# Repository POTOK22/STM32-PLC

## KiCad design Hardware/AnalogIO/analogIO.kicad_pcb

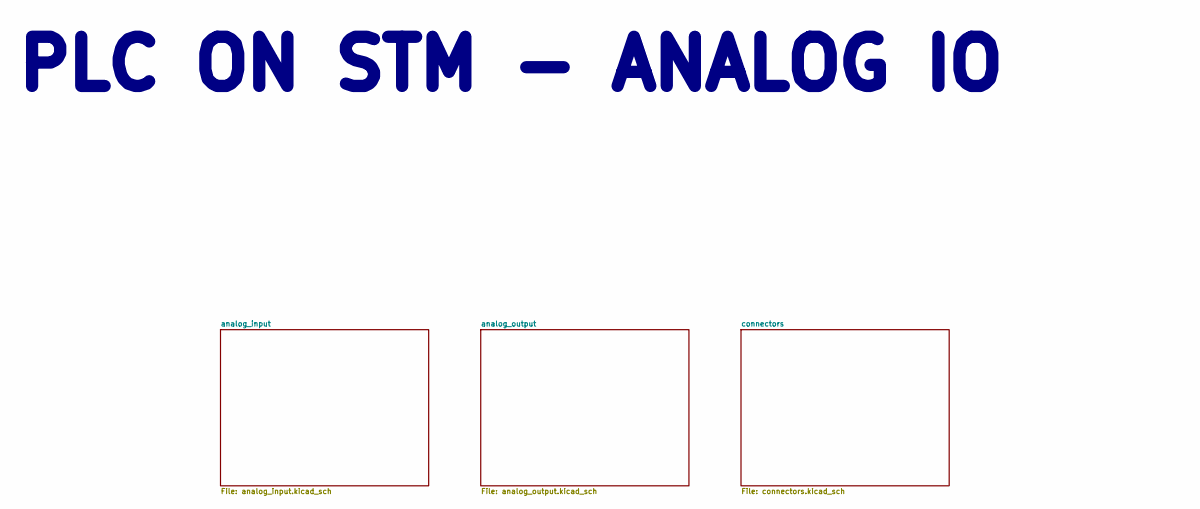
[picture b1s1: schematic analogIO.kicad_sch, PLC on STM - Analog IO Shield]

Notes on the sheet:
PLC ON STM - ANALOG IO

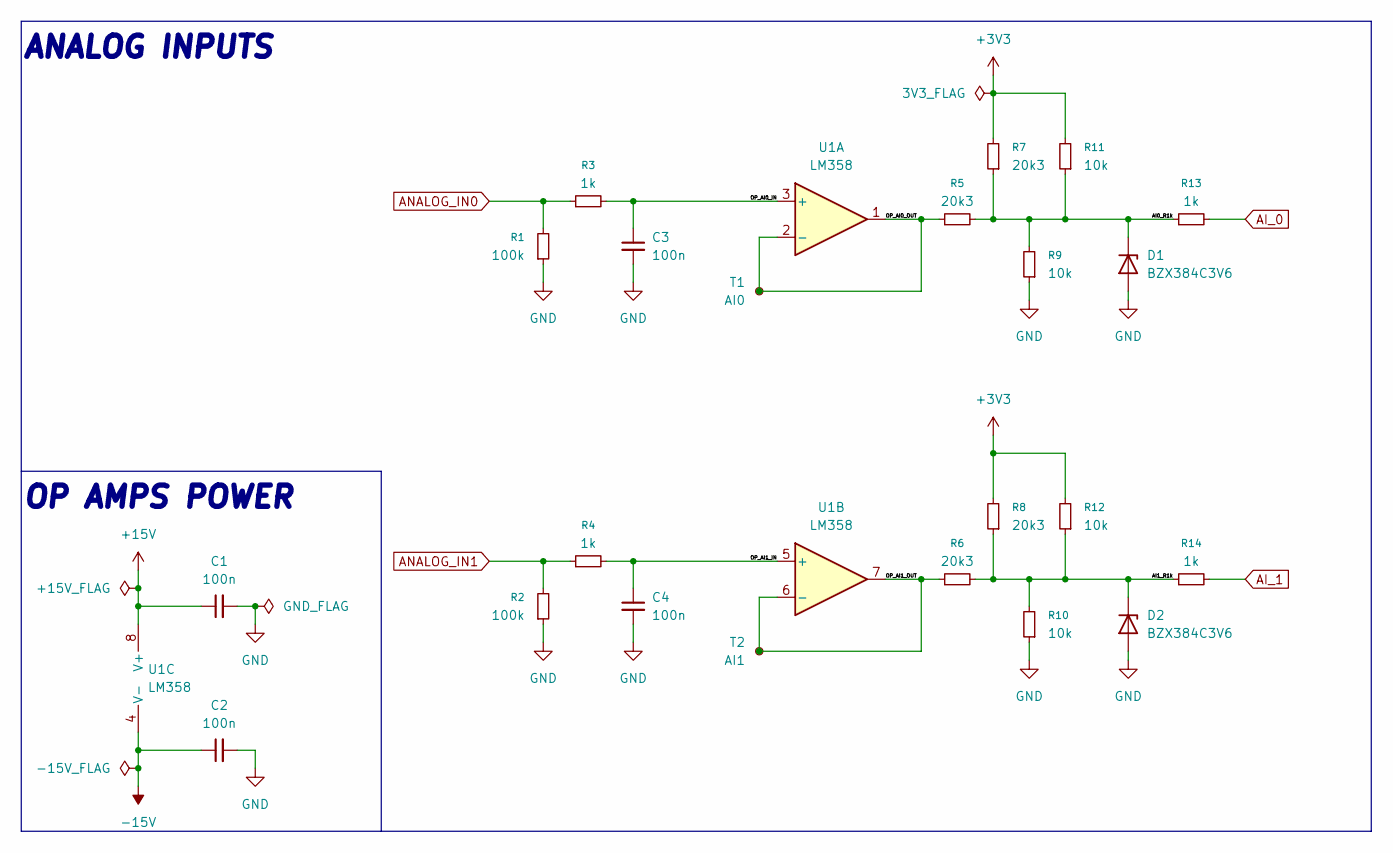
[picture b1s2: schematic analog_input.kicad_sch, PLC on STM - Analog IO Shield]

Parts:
C1, C2, C3, C4: 100n; C_0603_1608Metric_Pad1.08x0.95mm_HandSolder; Mouser Part Number GRM033R6YA104ME14D
D1, D2: BZX384C3V6; D_SOD-323; Mouser Part Number 78-BZX384C3V6-HE3-08
R1, R2: 100k; R_0603_1608Metric_Pad0.98x0.95mm_HandSolder; Mouser Part Number 603-RT0603DRE07100KL
R3, R4, R13, R14: 1k; R_0603_1608Metric_Pad0.98x0.95mm_HandSolder; Mouser Part Number 71-CRCW06031K00FKED
R5, R6, R7, R8: 20k3; R_0603_1608Metric_Pad0.98x0.95mm_HandSolder; Mouser Part Number 71-CRCW0603-20.5K-E3
R9, R10, R11, R12: 10k; R_0603_1608Metric_Pad0.98x0.95mm_HandSolder; Mouser Part Number 71-CRCW0603-10K-E3
T1: AI0; TestPoint_Pad_1.0x1.0mm
T2: AI1; TestPoint_Pad_1.0x1.0mm
U1: LM358; SOIC-8_3.9x4.9mm_P1.27mm; Mouser Part Number 511-LM358D

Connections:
+3V3: R7.2, R8.2, R11.2, R12.2; also elsewhere on the board
+15V: C1.1, U1.8 (V+); also elsewhere on the board
-15V: C2.1, U1.4 (V-); also elsewhere on the board
/analog_input/AI0_R1k: D1.1 (K), R5.2, R7.1, R9.2, R11.1, R13.1
/analog_input/AI1_R1k: D2.1 (K), R6.2, R8.1, R10.2, R12.1, R14.1
/analog_input/OP_AI0_IN: C3.1, R3.2, U1.3 (+)
/analog_input/OP_AI0_OUT: R5.1, T1.1, U1.1, U1.2 (-)
/analog_input/OP_AI1_IN: C4.1, R4.2, U1.5 (+)
/analog_input/OP_AI1_OUT: R6.1, T2.1, U1.6 (-), U1.7
AI_0: R13.2; also elsewhere on the board
AI_1: R14.2; also elsewhere on the board
ANALOG_IN0: R1.2, R3.1; also elsewhere on the board
ANALOG_IN1: R2.2, R4.1; also elsewhere on the board
GND: C1.2, C2.2, C3.2, C4.2, D1.2 (A), D2.2 (A), R1.1, R2.1, R9.1, R10.1; also elsewhere on the board

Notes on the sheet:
OP AMPS POWER
ANALOG INPUTS

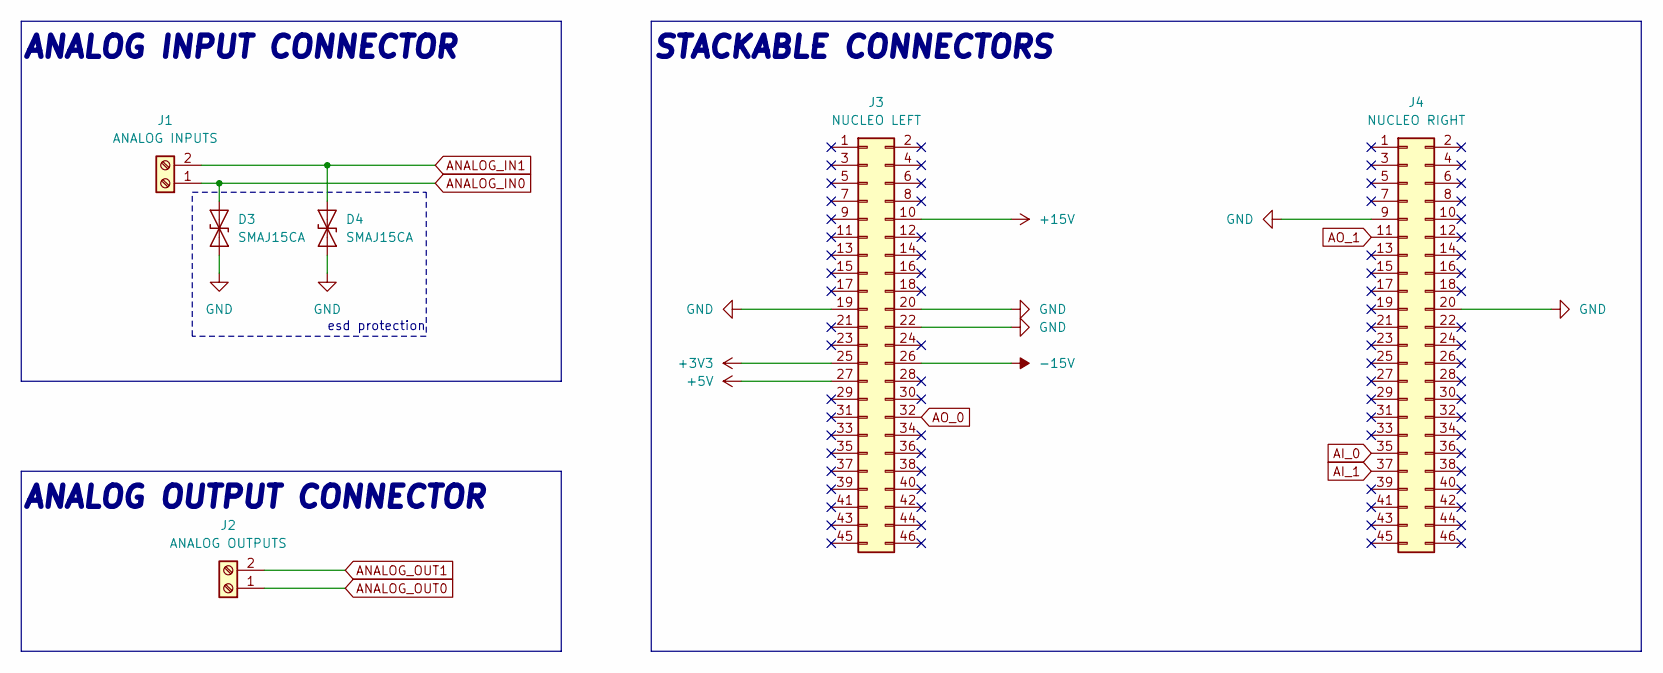
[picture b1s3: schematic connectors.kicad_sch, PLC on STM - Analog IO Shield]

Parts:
D3, D4: SMAJ15CA; D_SMA; Mouser Part Number 576-SMBJ15CA
J1: ANALOG INPUTS; 1725656; Mouser Part Number 651-1725656
J2: ANALOG OUTPUTS; 1725656; Mouser Part Number 651-1725656
J3: NUCLEO LEFT; PRT12790; Mouser Part Number 474-PRT-12790
J4: NUCLEO RIGHT; PRT12790; Mouser Part Number 474-PRT-12790

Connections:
+3V3: J3.25; also elsewhere on the board
+5V: J3.27; also elsewhere on the board
+15V: J3.10; also elsewhere on the board
-15V: J3.26; also elsewhere on the board
AI_0: J4.35; also elsewhere on the board
AI_1: J4.37; also elsewhere on the board
ANALOG_IN0: D3.2 (A2), J1.1; also elsewhere on the board
ANALOG_IN1: D4.2 (A2), J1.2; also elsewhere on the board
ANALOG_OUT0: J2.1; also elsewhere on the board
ANALOG_OUT1: J2.2; also elsewhere on the board
AO_0: J3.32; also elsewhere on the board
AO_1: J4.11; also elsewhere on the board
GND: D3.1 (A1), D4.1 (A1), J3.19, J3.20, J3.22, J4.9, J4.20; also elsewhere on the board

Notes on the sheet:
ANALOG INPUT CONNECTOR
STACKABLE CONNECTORS
esd protection
ANALOG OUTPUT CONNECTOR

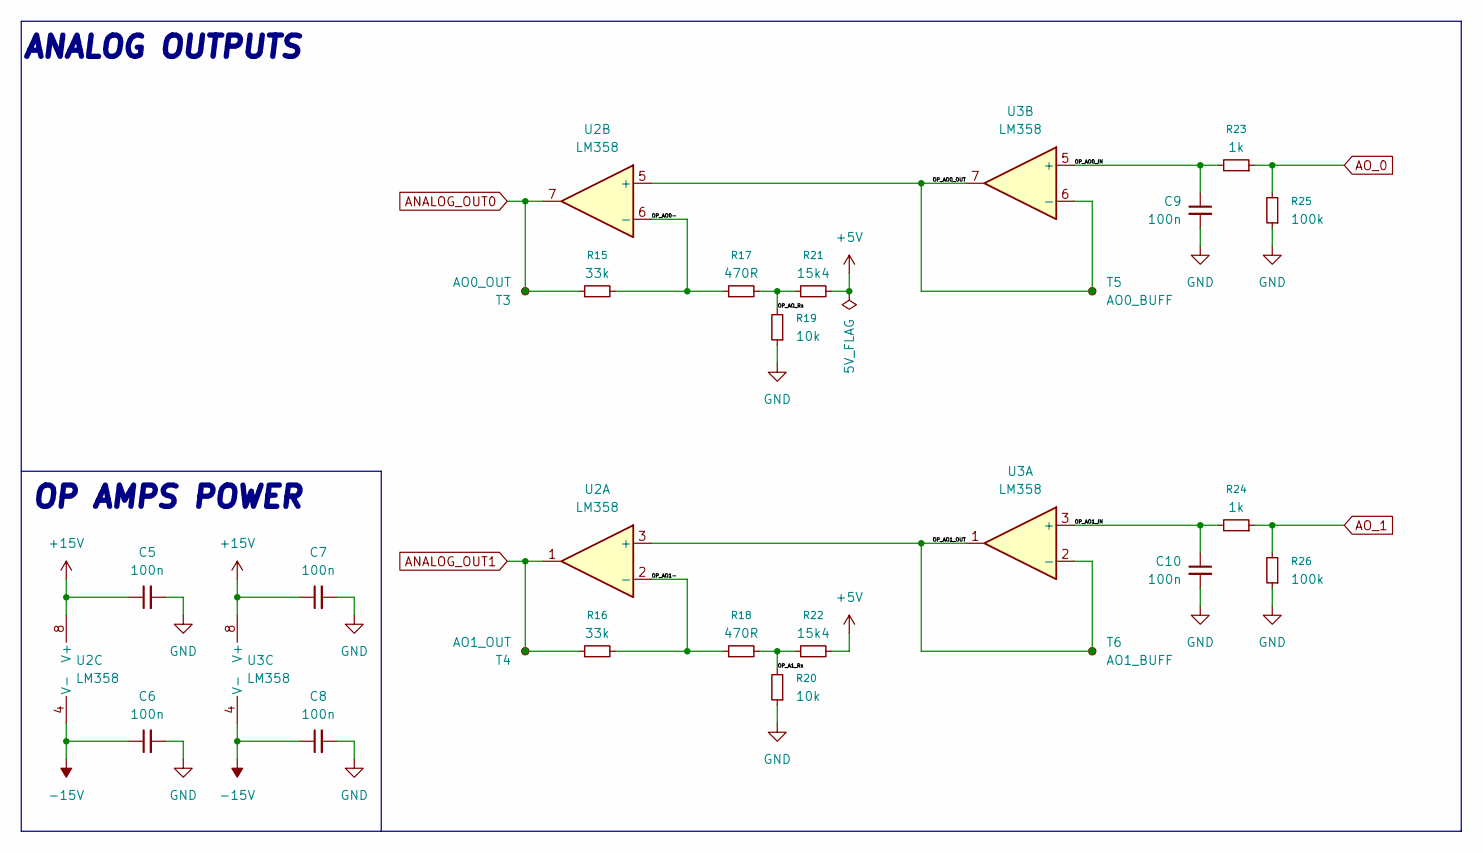
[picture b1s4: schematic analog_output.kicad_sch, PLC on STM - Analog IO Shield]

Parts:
C5, C6, C7, C8, C9, C10: 100n; C_0603_1608Metric_Pad1.08x0.95mm_HandSolder; Mouser Part Number GRM033R6YA104ME14D
R15, R16: 33k; R_0603_1608Metric_Pad0.98x0.95mm_HandSolder; Mouser Part Number 71-CRCW0603-33K-E3
R17, R18: 470R; R_0603_1608Metric_Pad0.98x0.95mm_HandSolder; Mouser Part Number 71-CRCW0603-470-E3
R19, R20: 10k; R_0603_1608Metric_Pad0.98x0.95mm_HandSolder; Mouser Part Number 71-CRCW0603-10K-E3
R21, R22: 15k4; R_0603_1608Metric_Pad0.98x0.95mm_HandSolder; Mouser Part Number 71-CRCW0603-15.4K-E3
R23, R24: 1k; R_0603_1608Metric_Pad0.98x0.95mm_HandSolder; Mouser Part Number 71-CRCW06031K00FKED
R25, R26: 100k; R_0603_1608Metric_Pad0.98x0.95mm_HandSolder; Mouser Part Number 603-RT0603DRE07100KL
T3: AO0_OUT; TestPoint_Pad_1.0x1.0mm
T4: AO1_OUT; TestPoint_Pad_1.0x1.0mm
T5: AO0_BUFF; TestPoint_Pad_1.0x1.0mm
T6: AO1_BUFF; TestPoint_Pad_1.0x1.0mm
U2, U3: LM358; SOIC-8_3.9x4.9mm_P1.27mm; Mouser Part Number 511-LM358D

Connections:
+5V: R21.2, R22.2; also elsewhere on the board
+15V: C5.1, C7.1, U2.8 (V+), U3.8 (V+); also elsewhere on the board
-15V: C6.1, C8.1, U2.4 (V-), U3.4 (V-); also elsewhere on the board
/analog_output/OP_A1_Rs: R18.2, R20.2, R22.1
/analog_output/OP_AO0-: R15.2, R17.1, U2.6 (-)
/analog_output/OP_AO0_IN: C9.1, R23.2, U3.5 (+)
/analog_output/OP_AO0_OUT: T5.1, U2.5 (+), U3.6 (-), U3.7
/analog_output/OP_AO1-: R16.2, R18.1, U2.2 (-)
/analog_output/OP_AO1_IN: C10.1, R24.2, U3.3 (+)
/analog_output/OP_AO1_OUT: T6.1, U2.3 (+), U3.1, U3.2 (-)
/analog_output/OP_AO_Rs: R17.2, R19.2, R21.1
ANALOG_OUT0: R15.1, T3.1, U2.7; also elsewhere on the board
ANALOG_OUT1: R16.1, T4.1, U2.1; also elsewhere on the board
AO_0: R23.1, R25.2; also elsewhere on the board
AO_1: R24.1, R26.2; also elsewhere on the board
GND: C5.2, C6.2, C7.2, C8.2, C9.2, C10.2, R19.1, R20.1, R25.1, R26.1; also elsewhere on the board

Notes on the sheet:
ANALOG OUTPUTS
OP AMPS POWER

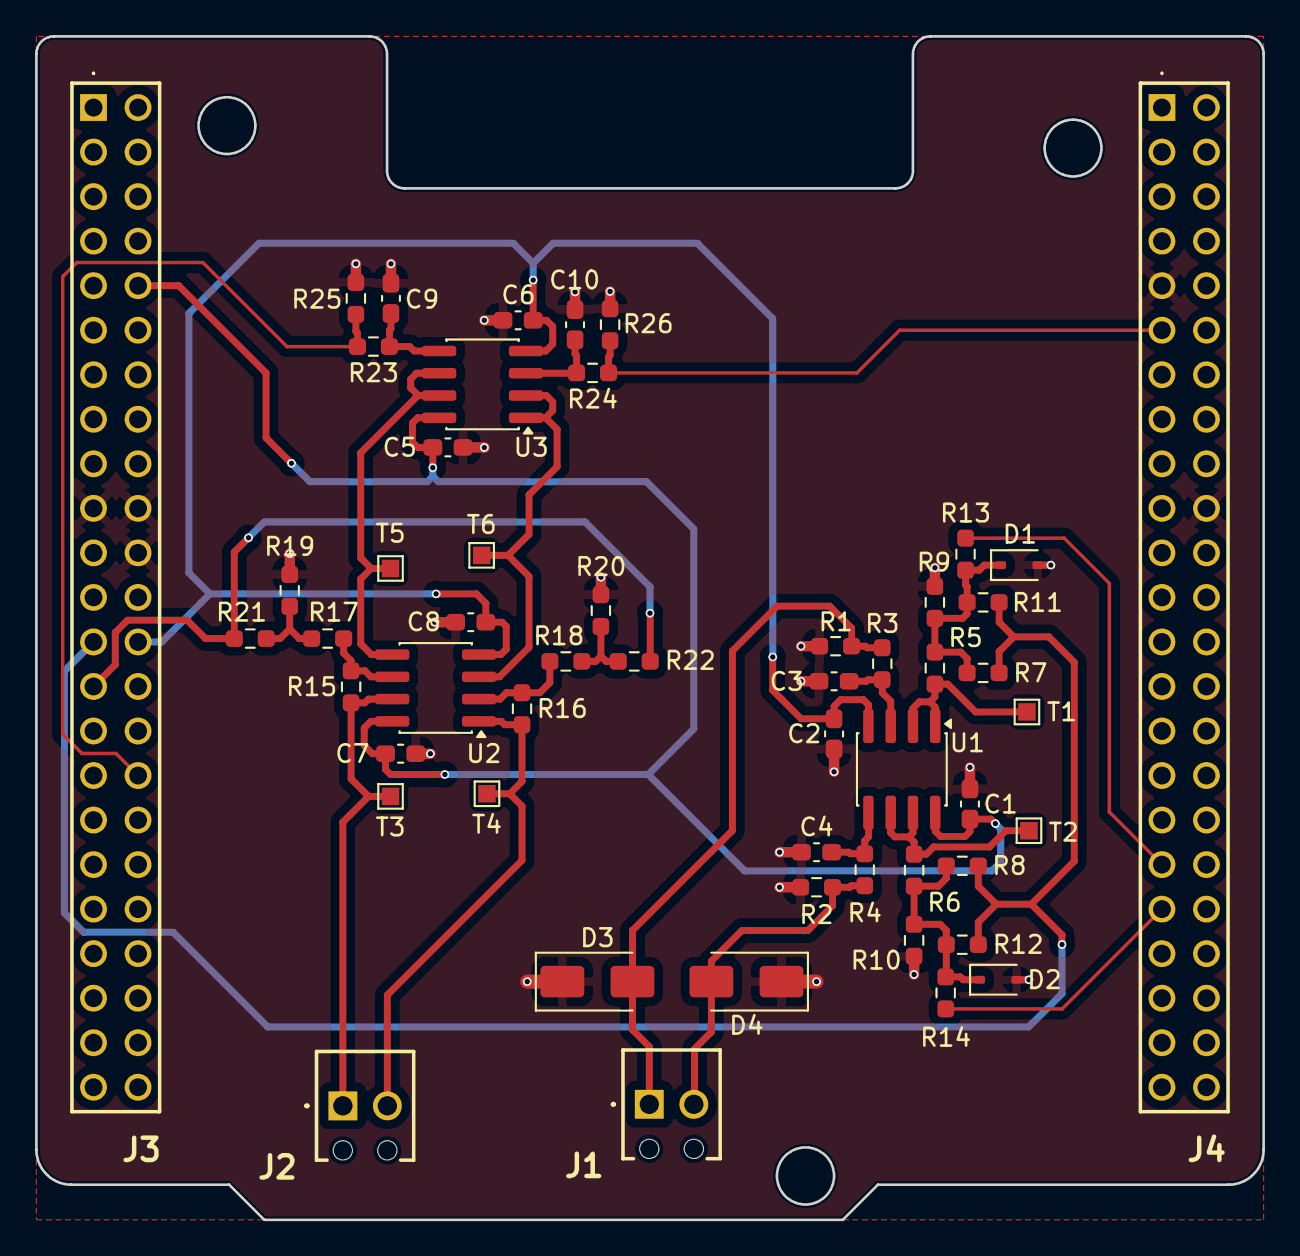
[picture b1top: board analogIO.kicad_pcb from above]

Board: 4 copper layers, 70.0 x 67.5 mm, 53 parts (0 on the bottom side), 27 nets.

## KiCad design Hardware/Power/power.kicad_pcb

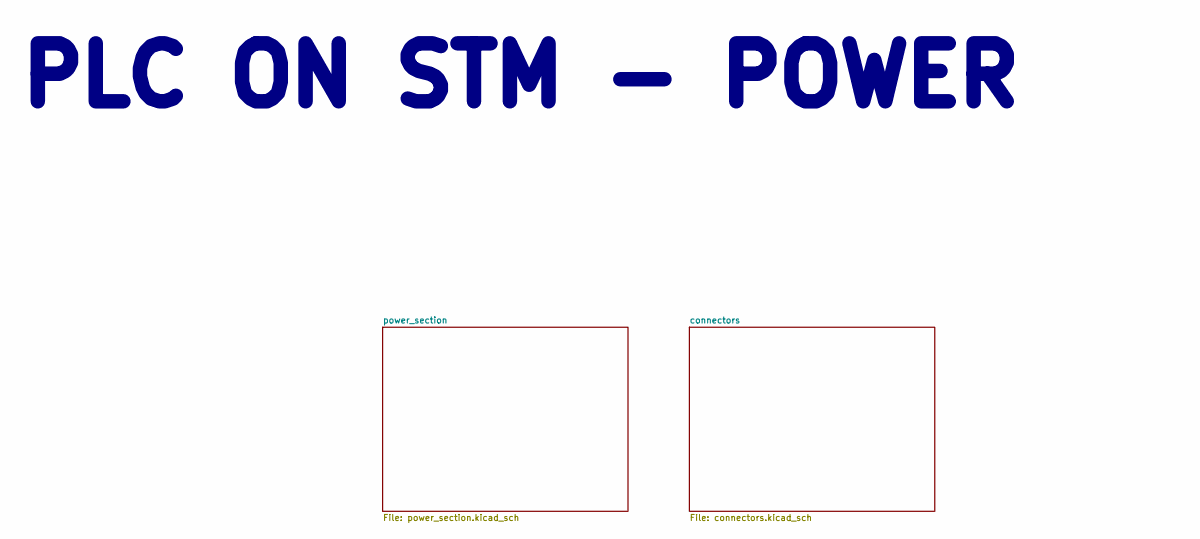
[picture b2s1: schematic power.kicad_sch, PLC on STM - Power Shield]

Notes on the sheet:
PLC ON STM - POWER

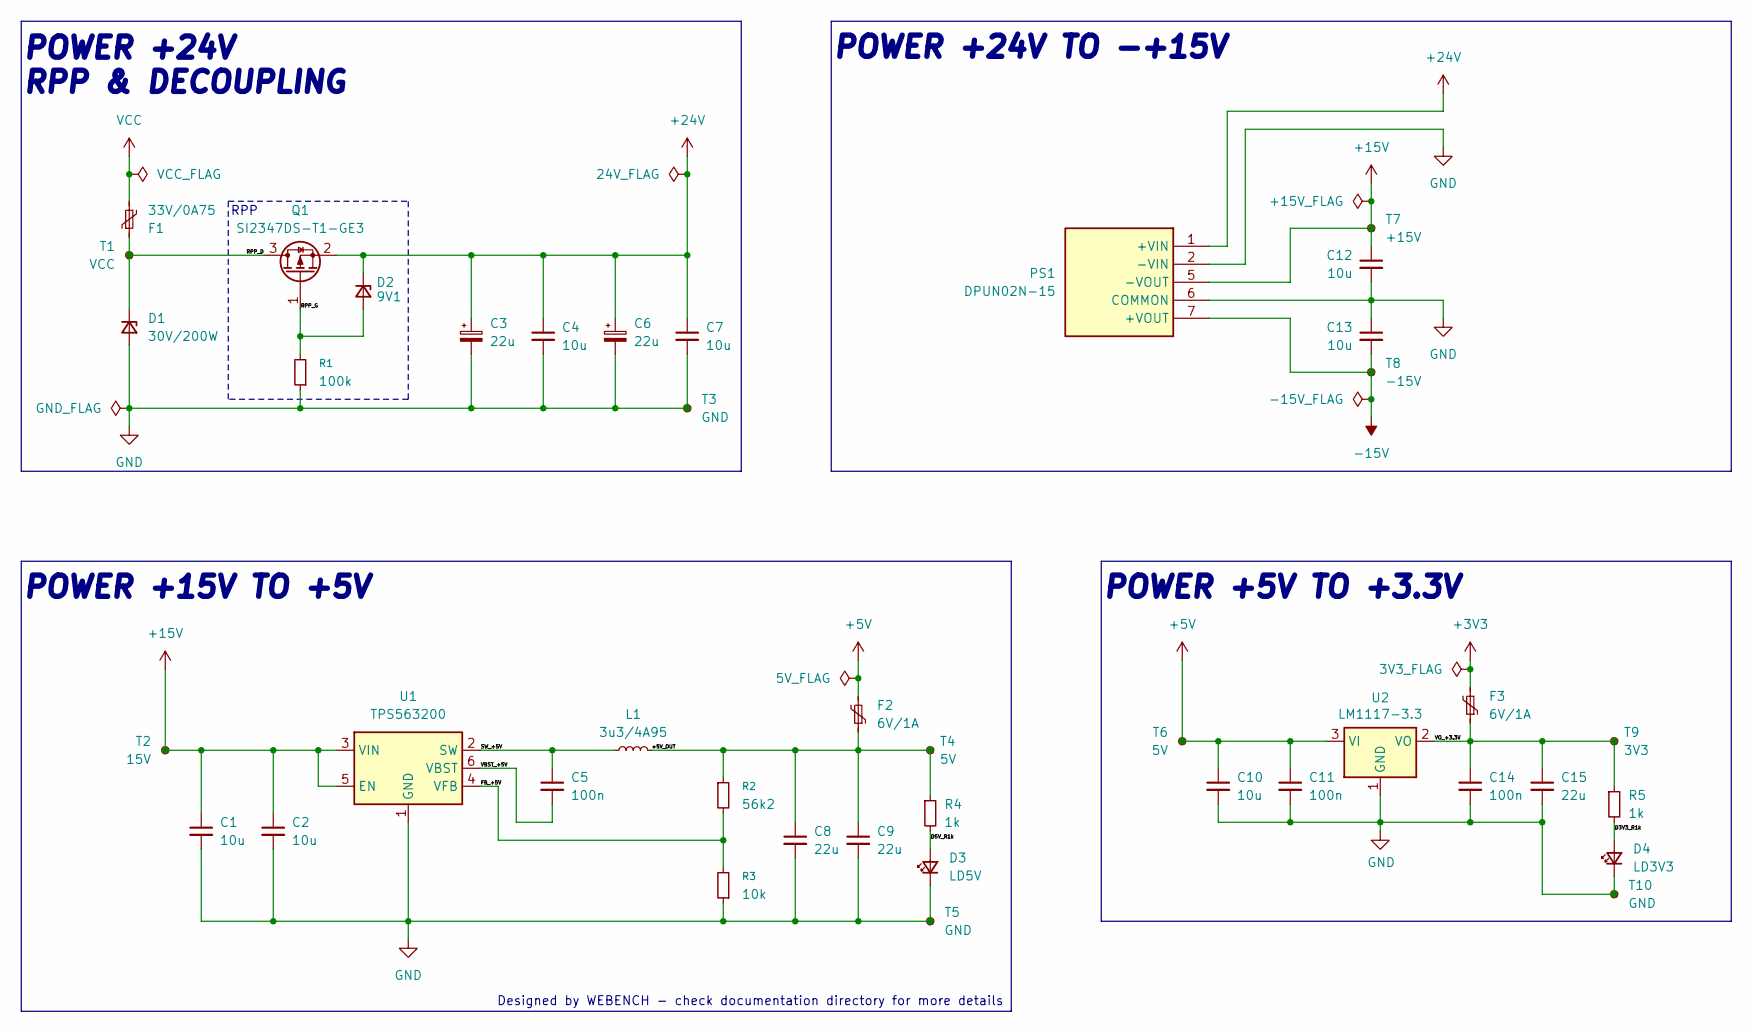
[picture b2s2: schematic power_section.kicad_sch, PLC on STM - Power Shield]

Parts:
C1, C2, C4, C7, C10, C12, C13: 10u; C_0603_1608Metric_Pad1.08x0.95mm_HandSolder; Mouser Part Number 81-GRM188R6YA106MA3J
C3, C6: 22u; CP_Elec_4x5.8; Mouser Part Number 647-UCM1V220MCL1GS
C5, C11, C14: 100n; C_0603_1608Metric_Pad1.08x0.95mm_HandSolder; Mouser Part Number GRM033R6YA104ME14D
C8, C9, C15: 22u; C_0603_1608Metric_Pad1.08x0.95mm_HandSolder; Mouser Part Number 810-C2012X5R1V226MAC
D1: 30V/200W; D_SOD-123; Mouser Part Number 750-TV02W260-G
D2: 9V1; D_SOD-323_HandSoldering; Mouser Part Number 833-MMXZ5239B-TP
D3: LD5V; LED_0603_1608Metric_Pad1.05x0.95mm_HandSolder
D4: LD3V3; LED_0603_1608Metric_Pad1.05x0.95mm_HandSolder
F1: 33V/0A75; Fuse_2920_7451Metric_Pad2.10x5.45mm_HandSolder; Mouser Part Number 530-0ZCF0075AF2C
F2, F3: 6V/1A; Fuse_0805_2012Metric_Pad1.15x1.40mm_HandSolder; Mouser Part Number 650-PICOSMDC050S-2
L1: 3u3/4A95; L_TDK_VLS6045EX_VLS6045AF; Mouser Part Number 810-VLS6045EX-3R3N
PS1: DPUN02N-15; DPUN02N15; Mouser Part Number 709-DPUN02N-15
Q1: SI2347DS-T1-GE3; SOT-23-3; Mouser Part Number 78-SI2347DS-T1-GE3
R1: 100k; R_0603_1608Metric_Pad0.98x0.95mm_HandSolder; Mouser Part Number 603-RT0603DRE07100KL
R2: 56k2; R_0603_1608Metric_Pad0.98x0.95mm_HandSolder; Mouser Part Number 71-CRCW060356K2FKEAH
R3: 10k; R_0603_1608Metric_Pad0.98x0.95mm_HandSolder; Mouser Part Number 71-CRCW0603-10K-E3
R4, R5: 1k; R_0603_1608Metric_Pad0.98x0.95mm_HandSolder; Mouser Part Number 71-CRCW06031K00FKED
T1: VCC; TestPoint_Pad_1.0x1.0mm
T2: 15V; TestPoint_Pad_1.0x1.0mm
T3, T5, T10: GND; TestPoint_Pad_1.0x1.0mm
T4, T6: 5V; TestPoint_Pad_1.0x1.0mm
T7: +15V; TestPoint_Pad_1.0x1.0mm
T8: -15V; TestPoint_Pad_1.0x1.0mm
T9: 3V3; TestPoint_Pad_1.0x1.0mm
U1: TPS563200; SOT-23-6; Mouser Part Number 595-TPS563200DDCR
U2: LM1117-3.3; SOT-223-3_TabPin2; Mouser Part Number 926-LM1117MPX3.3NOPB

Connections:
+3V3: F3.2; also elsewhere on the board
+5V: C10.1, C11.1, F2.2, T6.1, U2.3 (VI); also elsewhere on the board
+15V: C1.1, C2.1, C12.1, PS1.5 (-VOUT), T2.1, T7.1, U1.3 (VIN), U1.5 (EN); also elsewhere on the board
+24V: C3.1, C4.1, C6.1, C7.1, D2.1 (K), PS1.1 (+VIN), Q1.2 (S); also elsewhere on the board
-15V: C13.2, PS1.7 (+VOUT), T8.1; also elsewhere on the board
/power_section/+5V_OUT: C8.1, C9.1, F2.1, L1.2, R2.1, R4.1, T4.1
/power_section/D3V3_R1k: D4.2 (A), R5.2
/power_section/D5V_R1k: D3.2 (A), R4.2
/power_section/FB_+5V: R2.2, R3.2, U1.4 (VFB)
/power_section/RPP_D: D1.1 (K), F1.1, Q1.3 (D), T1.1
/power_section/RPP_G: D2.2 (A), Q1.1 (G), R1.2
/power_section/SW_+5V: C5.1, L1.1, U1.2 (SW)
/power_section/VBST_+5V: C5.2, U1.6 (VBST)
/power_section/VO_+3.3V: C14.1, C15.1, F3.1, R5.1, T9.1, U2.2 (VO)
GND: C1.2, C2.2, C3.2, C4.2, C6.2, C7.2, C8.2, C9.2, C10.2, C11.2, C12.2, C13.1, C14.2, C15.2, D1.2 (A), D3.1 (K), D4.1 (K), PS1.2 (-VIN), PS1.6 (COMMON), R1.1, R3.1, T3.1, T5.1, T10.1, U1.1 (GND), U2.1 (GND); also elsewhere on the board
VCC: F1.2; also elsewhere on the board

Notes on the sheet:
POWER +24V TO -+15V
POWER +15V TO +5V
RPP
POWER +24V RPP & DECOUPLING
POWER +5V TO +3.3V
Designed by WEBENCH - check documentation directory for more details

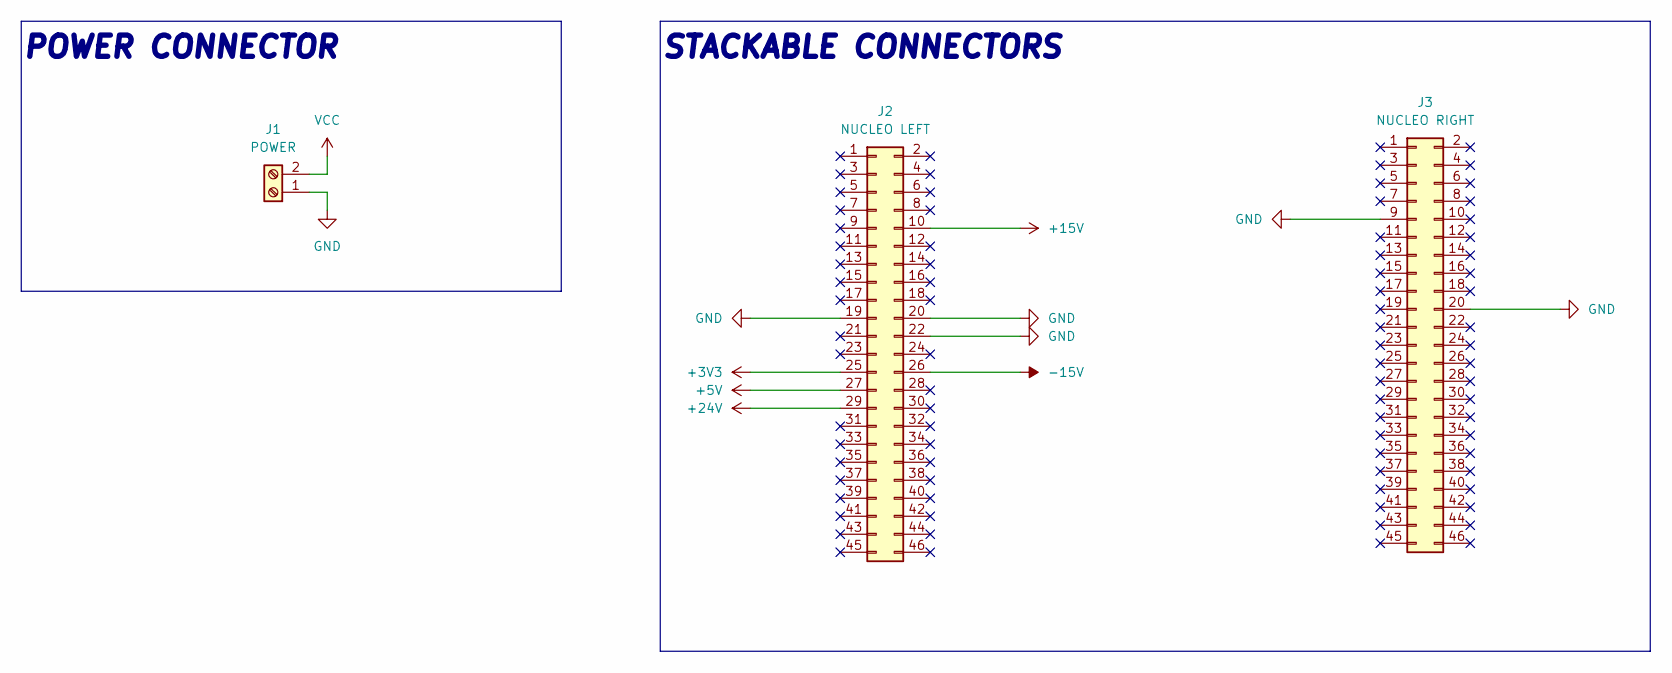
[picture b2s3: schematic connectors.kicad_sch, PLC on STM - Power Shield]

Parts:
J1: POWER; 1725656; Mouser Part Number 651-1725656
J2: NUCLEO LEFT; PRT12790; Mouser Part Number 474-PRT-12790
J3: NUCLEO RIGHT; PRT12790; Mouser Part Number 474-PRT-12790

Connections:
+3V3: J2.25; also elsewhere on the board
+5V: J2.27; also elsewhere on the board
+15V: J2.10; also elsewhere on the board
+24V: J2.29; also elsewhere on the board
-15V: J2.26; also elsewhere on the board
GND: J1.1, J2.19, J2.20, J2.22, J3.9, J3.20; also elsewhere on the board
VCC: J1.2; also elsewhere on the board

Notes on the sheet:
POWER CONNECTOR
STACKABLE CONNECTORS

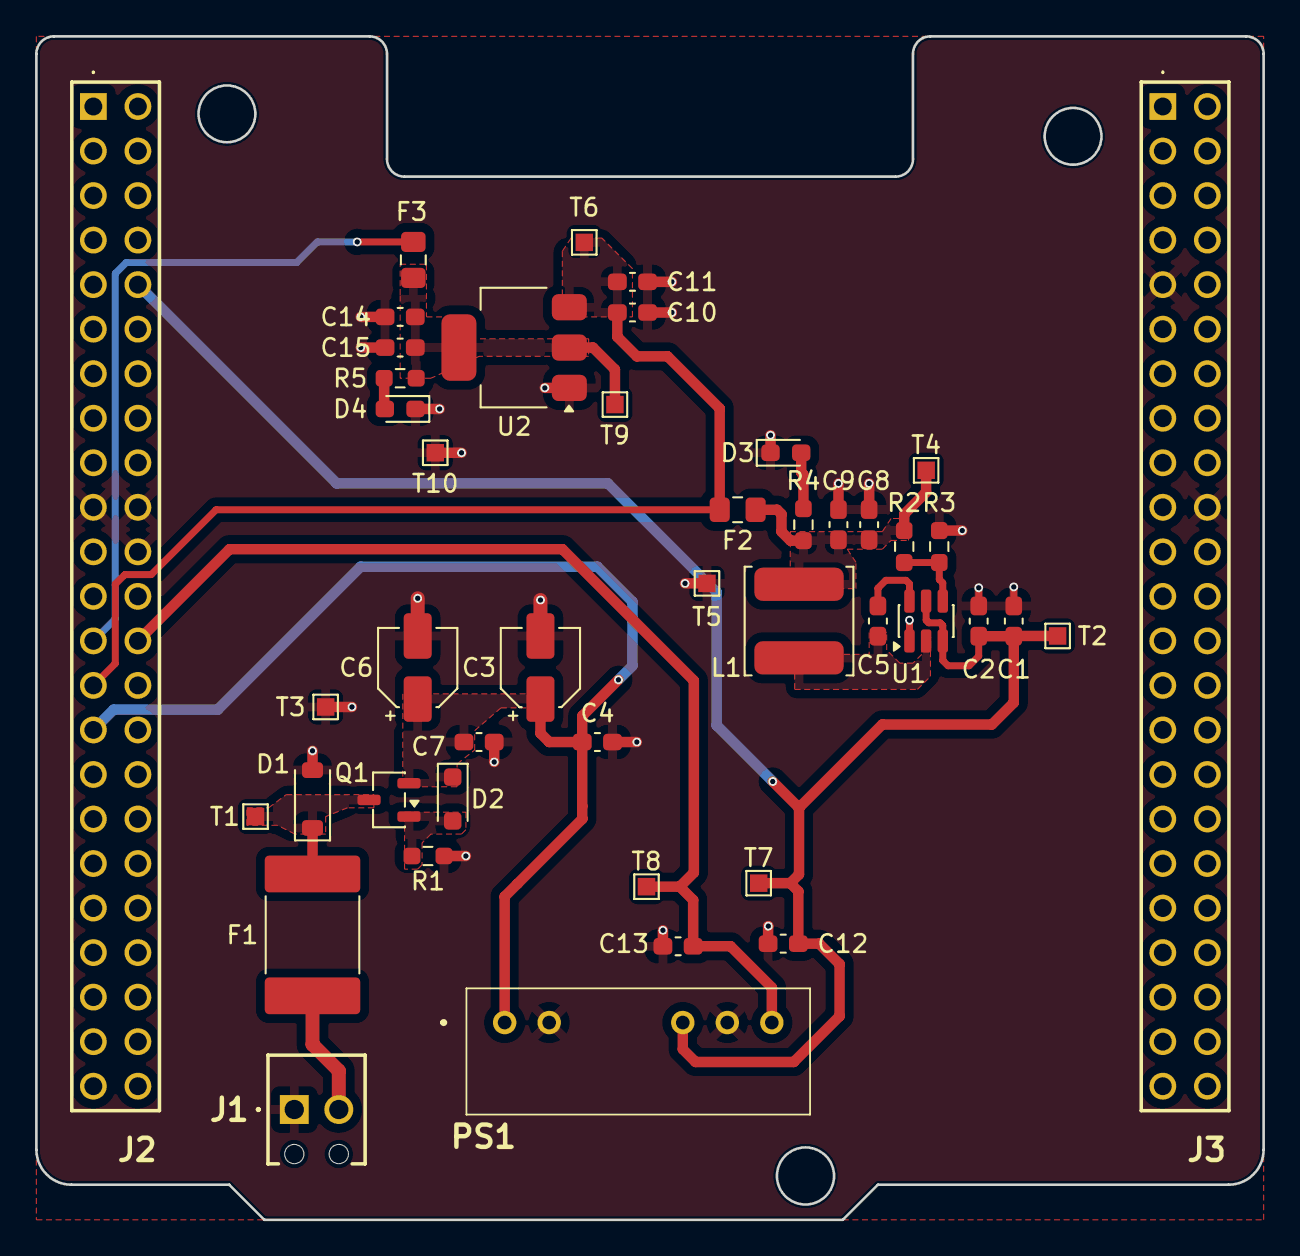
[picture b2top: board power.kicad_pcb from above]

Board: 4 copper layers, 70.0 x 67.5 mm, 45 parts (0 on the bottom side), 16 nets.

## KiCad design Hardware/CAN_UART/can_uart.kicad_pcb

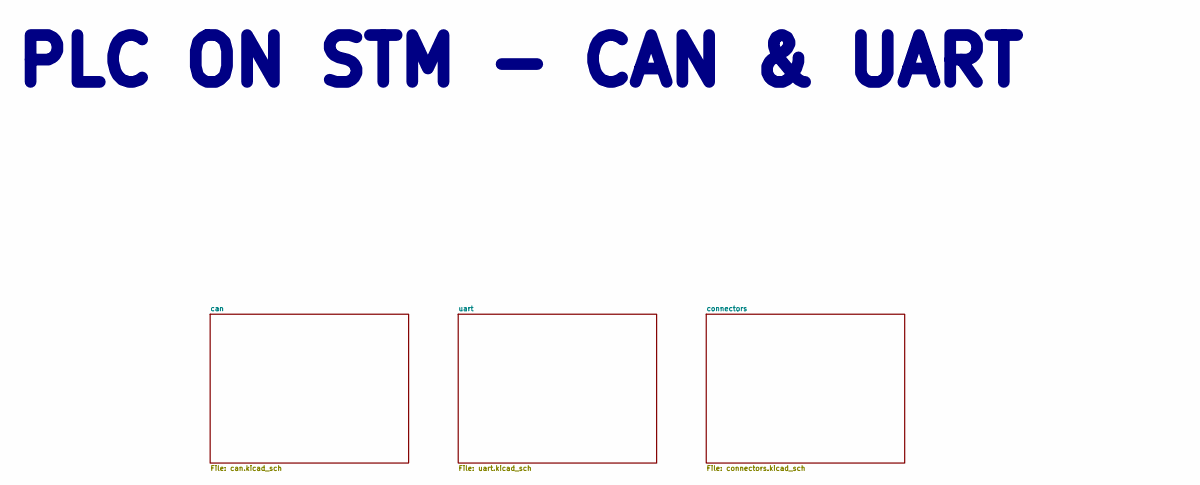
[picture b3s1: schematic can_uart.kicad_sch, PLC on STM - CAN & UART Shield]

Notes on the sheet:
PLC ON STM - CAN & UART

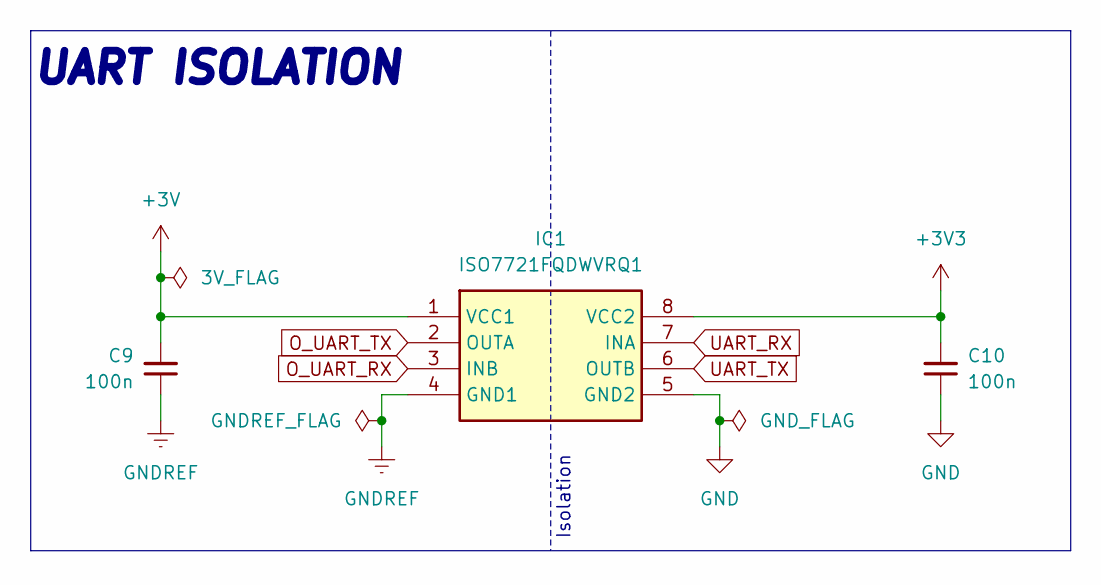
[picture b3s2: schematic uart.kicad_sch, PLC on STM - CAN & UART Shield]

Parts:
C9, C10: 100n; C_0603_1608Metric_Pad1.08x0.95mm_HandSolder; Mouser Part Number GRM033R6YA104ME14D
IC1: ISO7721FQDWVRQ1; SOIC127P1150X280-8N; Manufacturer_Part_Number ISO7721FQDWVRQ1

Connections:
+3V: C9.2, IC1.1 (VCC1); also elsewhere on the board
+3V3: C10.2, IC1.8 (VCC2); also elsewhere on the board
GND: C10.1, IC1.5 (GND2); also elsewhere on the board
GNDREF: C9.1, IC1.4 (GND1); also elsewhere on the board
O_UART_RX: IC1.3 (INB); also elsewhere on the board
O_UART_TX: IC1.2 (OUTA); also elsewhere on the board
UART_RX: IC1.7 (INA); also elsewhere on the board
UART_TX: IC1.6 (OUTB); also elsewhere on the board

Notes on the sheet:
Isolation
UART ISOLATION

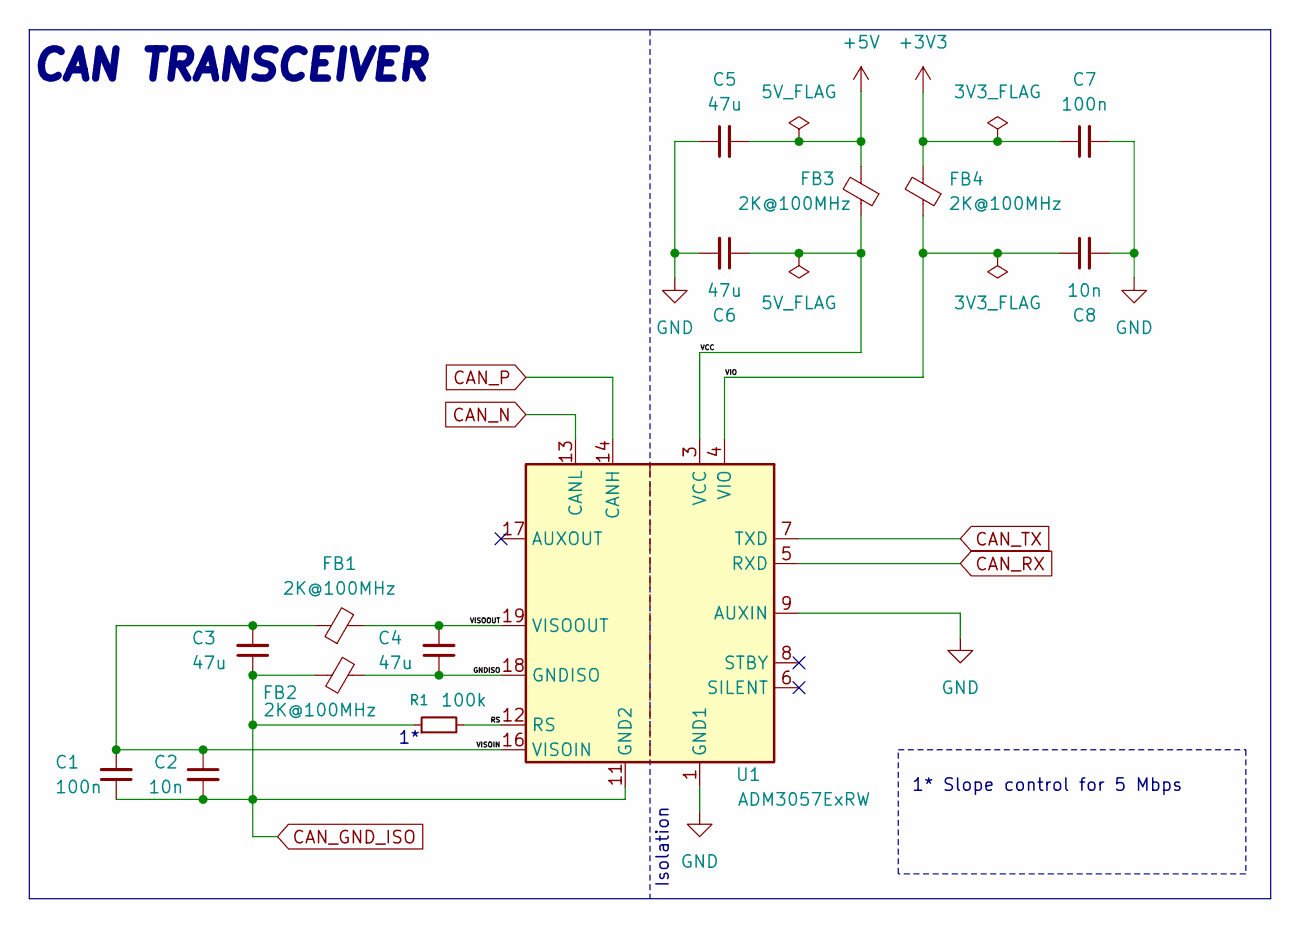
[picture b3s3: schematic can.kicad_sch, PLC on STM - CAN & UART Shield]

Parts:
C1, C7: 100n; C_0603_1608Metric_Pad1.08x0.95mm_HandSolder; Mouser Part Number GRM033R6YA104ME14D
C2, C8: 10n; C_0603_1608Metric_Pad1.08x0.95mm_HandSolder; Mouser Part Number 81-GRM1857U1A103JA4J
C3, C4, C5, C6: 47u; C_0805_2012Metric_Pad1.18x1.45mm_HandSolder; Mouser Part Number 81-GRM21BR60J476M01L
FB1, FB2, FB3, FB4: 2K@100MHz; L_0805_2012Metric_Pad1.05x1.20mm_HandSolder; Mouser Part Number 623-2508052027Y1
R1: 100k; R_0603_1608Metric_Pad0.98x0.95mm_HandSolder; Mouser Part Number 603-RT0603DRE07100KL
U1: ADM3057ExRW; SOIC-20W_7.5x12.8mm_P1.27mm; Mouser Part Number 584-ADM3057ETRWZ-EP

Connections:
+3V3: C7.1, FB4.2; also elsewhere on the board
+5V: C5.2, FB3.2; also elsewhere on the board
/can/GNDISO: C4.1, FB2.1, U1.18 (GNDISO), U1.20 (GNDISO)
/can/RS: R1.2, U1.12 (RS)
/can/VCC: C6.1, FB3.1, U1.3 (VCC)
/can/VIO: C8.1, FB4.1, U1.4 (VIO)
/can/VISOIN: C1.2, C2.1, C3.2, FB1.1, U1.16 (VISOIN)
/can/VISOOUT: C4.2, FB1.2, U1.19 (VISOOUT)
CAN_GND_ISO: C1.1, C2.2, C3.1, FB2.2, R1.1, U1.11 (GND2), U1.15 (GND2); also elsewhere on the board
CAN_N: U1.13 (CANL); also elsewhere on the board
CAN_P: U1.14 (CANH); also elsewhere on the board
CAN_RX: U1.5 (RXD); also elsewhere on the board
CAN_TX: U1.7 (TXD); also elsewhere on the board
GND: C5.1, C6.2, C7.2, C8.2, U1.1 (GND1), U1.2 (GND1), U1.9 (AUXIN), U1.10 (GND1); also elsewhere on the board

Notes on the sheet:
Isolation
CAN TRANSCEIVER
1* Slope control for 5 Mbps

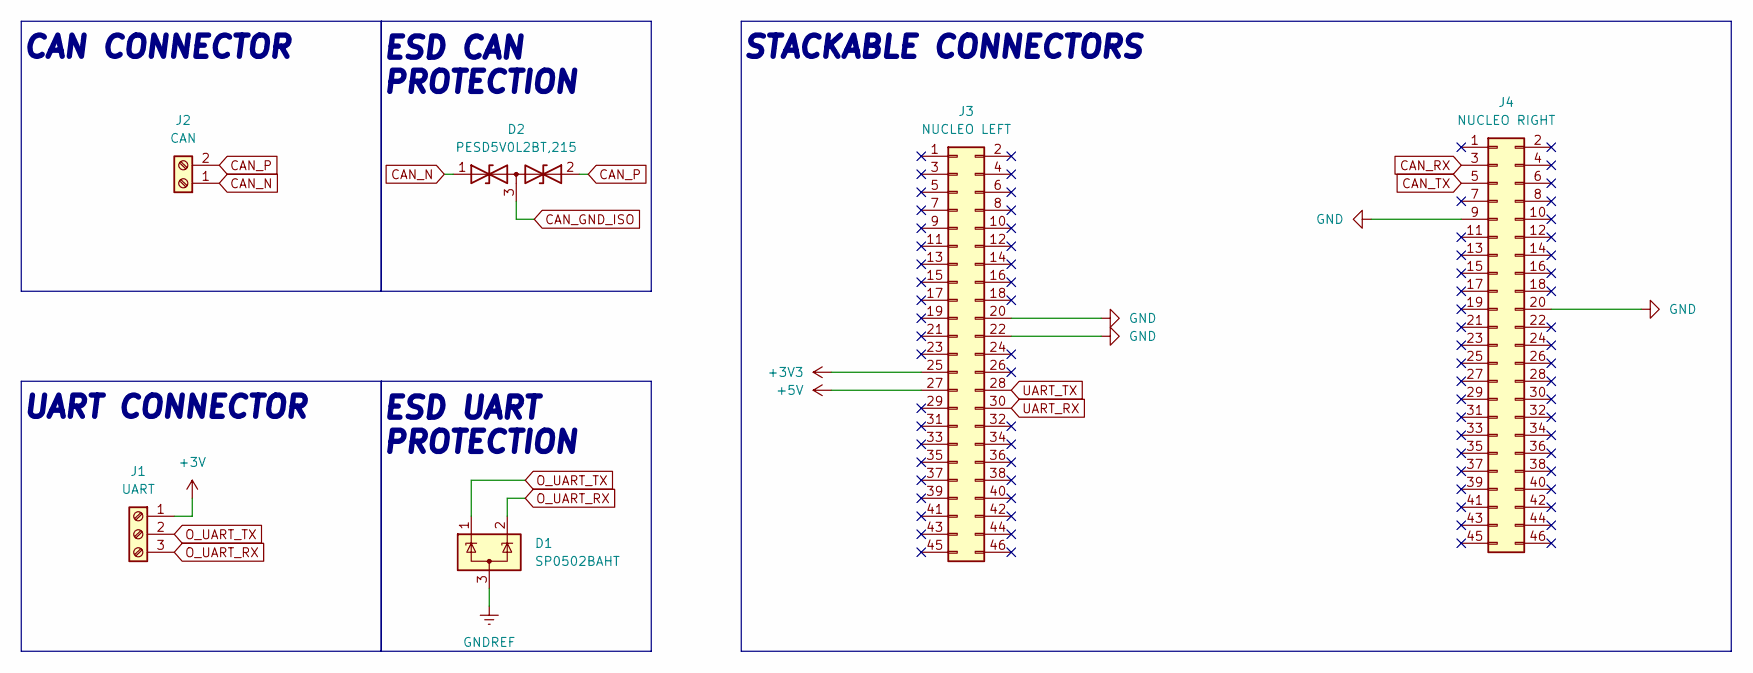
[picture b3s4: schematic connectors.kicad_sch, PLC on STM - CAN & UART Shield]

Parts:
D1: SP0502BAHT; SOT-23
D2: PESD5V0L2BT,215; SOT-23-3; Mouser Part Number 771-PESD5V0L2BT-T/R
J1: UART; 1725669
J2: CAN; 1725656; Mouser Part Number 651-1725656
J3: NUCLEO LEFT; PRT12790; Mouser Part Number 474-PRT-12790
J4: NUCLEO RIGHT; PRT12790; Mouser Part Number 474-PRT-12790

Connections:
+3V: J1.1; also elsewhere on the board
+3V3: J3.25; also elsewhere on the board
+5V: J3.27; also elsewhere on the board
CAN_GND_ISO: D2.3 (common); also elsewhere on the board
CAN_N: D2.1 (A1), J2.1; also elsewhere on the board
CAN_P: D2.2 (A2), J2.2; also elsewhere on the board
CAN_RX: J4.3; also elsewhere on the board
CAN_TX: J4.5; also elsewhere on the board
GND: J3.20, J3.22, J4.9, J4.20; also elsewhere on the board
GNDREF: D1.3 (A); also elsewhere on the board
O_UART_RX: D1.2 (K), J1.3; also elsewhere on the board
O_UART_TX: D1.1 (K), J1.2; also elsewhere on the board
UART_RX: J3.30; also elsewhere on the board
UART_TX: J3.28; also elsewhere on the board

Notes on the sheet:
UART CONNECTOR
CAN CONNECTOR
ESD UART PROTECTION
ESD CAN PROTECTION
STACKABLE CONNECTORS
